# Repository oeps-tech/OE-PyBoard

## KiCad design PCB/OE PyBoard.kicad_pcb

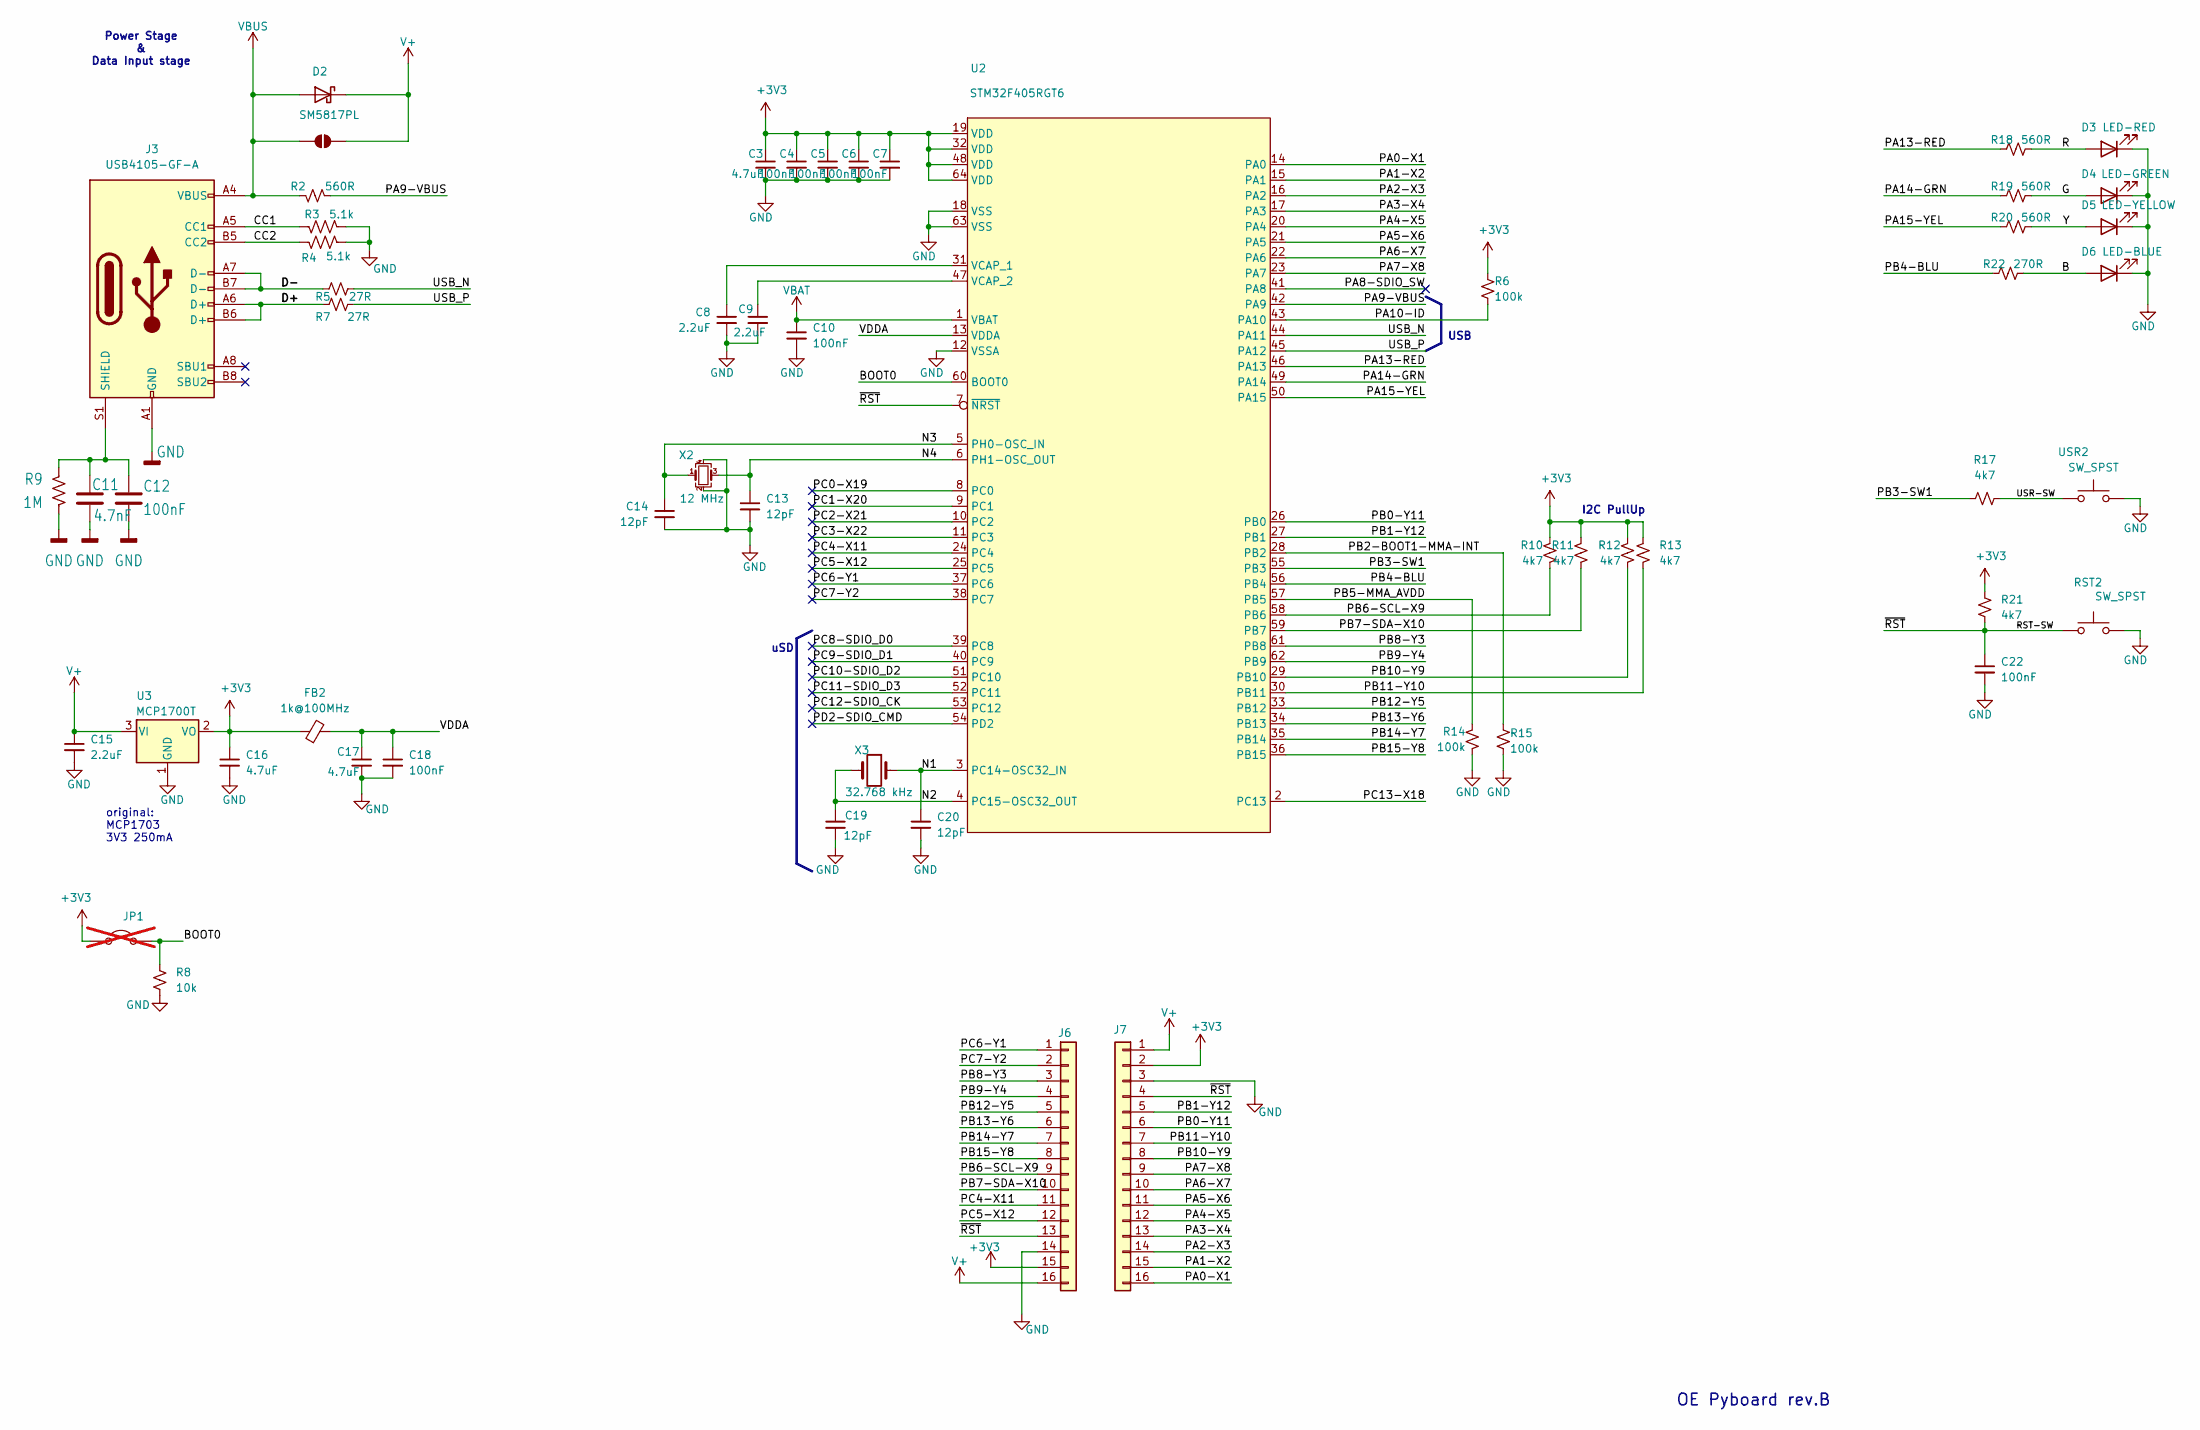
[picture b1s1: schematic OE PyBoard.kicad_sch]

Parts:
C3, C16, C17: 4.7uF; C_0603_1608Metric; MPN C1608X6S1C475K080AC
C4, C5, C6, C7, C10, C12, C18, C22: 100nF; C_0402_1005Metric; MPN CGA2B3X7R1H104K050BB
C8, C9, C15: 2.2uF; C_0603_1608Metric; MPN GRM188R61E225KA12D
C11: 4.7nF; C_0402_1005Metric; MPN 885012205084
C13, C14, C19, C20: 12pF; C_0402_1005Metric; MPN GRM1555C1H120JA01D
D2: SM5817PL; D_SOD-123; MPN SM5817PL-TP
D3: LED-RED; LED_0603_1608Metric; MPN 5990010007F
D4: LED-GREEN; LED_0603_1608Metric; MPN LSM0603453V
D5: LED-YELLOW; LED_0603_1608Metric; MPN 5990040007F
D6: LED-BLUE; LED_0603_1608Metric; MPN 5988D90107F
FB2: 1k@100MHz; L_0402_1005Metric; MPN BLM15HD102SN1D
J3: USB4105-GF-A; USB_C_Receptacle_GCT_USB4105-xx-A_16P_TopMnt_Horizontal; MPN USB4105-GF-A
J6, J7: Conn_01x08; PinHeader_1x16_P2.54mm_Vertical; MPN CES-116-01-T-S
JP1: Jumper; PinHeader_1x02_P2.54mm_Vertical; not fitted
JP2: 0R; SolderJumper-2_P1.3mm_Open_RoundedPad1.0x1.5mm
R2, R18, R19, R20: 560R; R_0402_1005Metric; MPN CRCW0402560RFKED
R3, R4: 5.1k; R_0402_1005Metric; MPN ERJ-2RKF5101X
R5, R7: 27R; R_0402_1005Metric; MPN RMCF0402FT27R0
R6, R14, R15: 100k; R_0402_1005Metric; MPN AC0402FR-07100KL
R8: 10k; R_0402_1005Metric; MPN ERJ-2RKF1002X
R9: 1M; R_0402_1005Metric; MPN CRCW04021M00FKED
R10, R11, R12, R13, R17, R21: 4k7; R_0402_1005Metric; MPN ERJ-2RKF4701X
R22: 270R; R_0402_1005Metric; MPN CRCW0402270RFKEDC
RST2: SW_SPST; SW_SPST_TL3305B; MPN TL3305BF260QG
U2: STM32F405RGT6; LQFP-64_10x10mm_P0.5mm; MPN STM32F405RGT6
U3: MCP1700T; SOT-23; MPN MCP1700T-3302E/TT
USR2: SW_SPST; SW_SPST_TL3305B; MPN TL3305BF260QG
X2: 12 MHz; Crystal_SMD_Abracon_ABM8AIG-4Pin_3.2x2.5mm; MPN ABM8AIG-12.000MHZ-12-2Z-T3
X3: 32.768 kHz; Crystal_SMD_2012-2Pin_2.0x1.2mm_HandSoldering; MPN 9HT11-32.768KBZF-T

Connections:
+3V3: C3.1, C4.1, C5.1, C6.1, C7.1, C16.1, FB2.1, J6.15, J7.2, JP1.2 (B), R6.1, R10.1, R11.1, R12.1, R13.1, R21.2, U2.19 (VDD), U2.32 (VDD), U2.48 (VDD), U2.64 (VDD), U3.2 (VO)
/B: D6.2 (A), R22.2
/BOOT0: JP1.1 (A), R8.1, U2.60 (BOOT0)
/CC1: J3.A5 (CC1), R3.1
/CC2: J3.B5 (CC2), R4.1
/D+: J3.A6 (D+), J3.B6 (D+), R7.2
/D-: J3.A7 (D-), J3.B7 (D-), R5.2
/G: D4.2 (A), R19.2
/N3: C14.1, U2.5 (PH0-OSC_IN), X2.1
/N4: C13.1, U2.6 (PH1-OSC_OUT), X2.3
/PA0-X1: J7.16, U2.14 (PA0)
/PA1-X2: J7.15, U2.15 (PA1)
/PA2-X3: J7.14, U2.16 (PA2)
/PA3-X4: J7.13, U2.17 (PA3)
/PA4-X5: J7.12, U2.20 (PA4)
/PA5-X6: J7.11, U2.21 (PA5)
/PA6-X7: J7.10, U2.22 (PA6)
/PA7-X8: J7.9, U2.23 (PA7)
/PA8-SDIO_SW: U2.41 (PA8)
/PA9-VBUS: R2.1, U2.42 (PA9)
/PA10-ID: R6.2, U2.43 (PA10)
/PA13-RED: R18.1, U2.46 (PA13)
/PA14-GRN: R19.1, U2.49 (PA14)
/PA15-YEL: R20.1, U2.50 (PA15)
/PB0-Y11: J7.6, U2.26 (PB0)
/PB1-Y12: J7.5, U2.27 (PB1)
/PB2-BOOT1-MMA-INT: R15.1, U2.28 (PB2)
/PB3-SW1: R17.1, U2.55 (PB3)
/PB4-BLU: R22.1, U2.56 (PB4)
/PB5-MMA_AVDD: R14.1, U2.57 (PB5)
/PB6-SCL-X9: J6.9, R10.2, U2.58 (PB6)
/PB7-SDA-X10: J6.10, R11.2, U2.59 (PB7)
/PB8-Y3: J6.3, U2.61 (PB8)
/PB9-Y4: J6.4, U2.62 (PB9)
/PB10-Y9: J7.8, R12.2, U2.29 (PB10)
/PB11-Y10: J7.7, R13.2, U2.30 (PB11)
/PB12-Y5: J6.5, U2.33 (PB12)
/PB13-Y6: J6.6, U2.34 (PB13)
/PB14-Y7: J6.7, U2.35 (PB14)
/PB15-Y8: J6.8, U2.36 (PB15)
/PC0-X19: U2.8 (PC0)
/PC1-X20: U2.9 (PC1)
/PC2-X21: U2.10 (PC2)
/PC3-X22: U2.11 (PC3)
/PC4-X11: J6.11, U2.24 (PC4)
/PC5-X12: J6.12, U2.25 (PC5)
/PC6-Y1: J6.1, U2.37 (PC6)
/PC7-Y2: J6.2, U2.38 (PC7)
/PC8-SDIO_D0: U2.39 (PC8)
/PC9-SDIO_D1: U2.40 (PC9)
/PC10-SDIO_D2: U2.51 (PC10)
/PC11-SDIO_D3: U2.52 (PC11)
/PC12-SDIO_CK: U2.53 (PC12)
/PC13-X18: U2.2 (PC13)
/PD2-SDIO_CMD: U2.54 (PD2)
/R: D3.2 (A), R18.2
/RST-SW: C22.1, J6.13, J7.4, R21.1, RST2.1, U2.7 (~NRST)
/USB_N: R5.1, U2.44 (PA11)
/USB_P: R7.1, U2.45 (PA12)
/USR-SW: R17.2, USR2.1
/VDDA: C17.1, C18.1, FB2.2, U2.13 (VDDA)
/Y: D5.2 (A), R20.2
GND: C3.2, C4.2, C5.2, C6.2, C7.2, C8.2, C9.2, C10.2, C11.2, C12.1, C13.2, C14.2, C15.2, C16.2, C17.2, C18.2, C19.2, C20.2, C22.2, D3.1 (K), D4.1 (K), D5.1 (K), D6.1 (K), J3.A1 (GND), J3.A12 (GND), J3.B1 (GND), J3.B12 (GND), J6.14, J7.3, R3.2, R4.2, R8.2, R9.1, R14.2, R15.2, RST2.2, U2.12 (VSSA), U2.18 (VSS), U2.63 (VSS), U3.1 (GND), USR2.2, X2.2, X2.4
unnamed: C11.1, C12.2, J3.S1 (SHIELD), R9.2
unnamed: C8.1, U2.31 (VCAP_1)
unnamed: C9.1, U2.47 (VCAP_2)
V+: C15.1, D2.1 (K), J6.16, J7.1, JP2.2 (B), U3.3 (VI)
VBAT: C10.1, U2.1 (VBAT)
VBUS: D2.2 (A), J3.A4 (VBUS), J3.A9 (VBUS), J3.B4 (VBUS), J3.B9 (VBUS), JP2.1 (A), R2.2

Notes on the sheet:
I2C PullUp
USB
original: MCP1703 3V3 250mA
uSD
OE Pyboard rev.B
Power Stage & Data Input stage

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
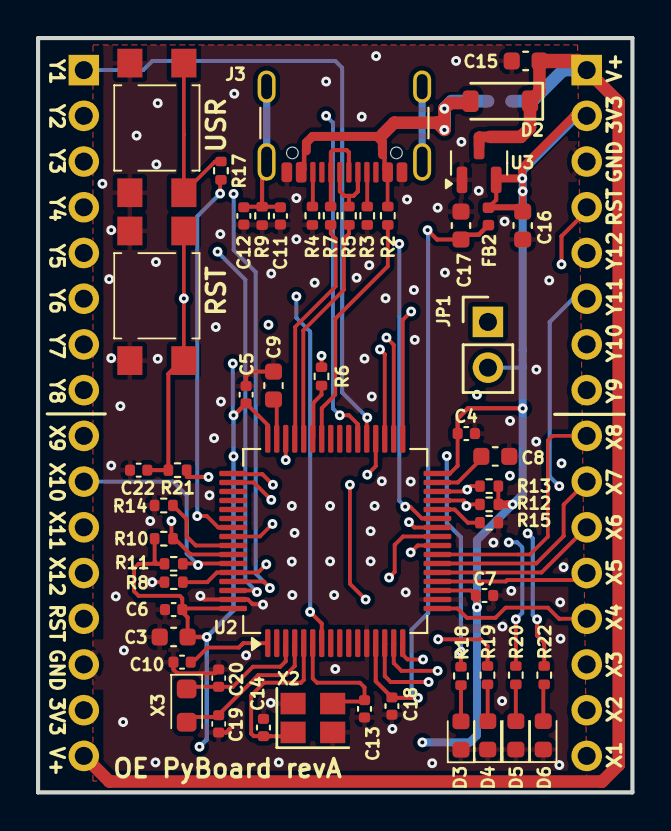
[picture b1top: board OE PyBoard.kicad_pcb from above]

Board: 4 copper layers, 33.0 x 41.9 mm, 56 parts (1 on the bottom side), 59 nets.

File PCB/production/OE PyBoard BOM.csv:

#;Reference;Qty;Value;Footprint;DNP;OEPSPN;MPN
1;C11;1;4.7nF;Capacitor_SMD:C_0402_1005Metric;;OEPS010017;885012205084
2;C13,C14,C19,C20;4;12pF;Capacitor_SMD:C_0402_1005Metric;;OEPS010086;GRM1555C1H120JA01D
3;C3,C16,C17;3;4.7uF;Capacitor_SMD:C_0603_1608Metric;;OEPS010018;C1608X6S1C475K080AC
4;C4,C5,C6,C7,C10,C12,C18,C22;8;100nF;Capacitor_SMD:C_0402_1005Metric;;OEPS010016;CGA2B3X7R1H104K050BB
5;C8,C9,C15;3;2.2uF;Capacitor_SMD:C_0603_1608Metric;;OEPS010075;GRM188R61E225KA12D
6;D2;1;SM5817PL;Diode_SMD:D_SOD-123;;OEPS030030;SM5817PL-TP
7;D3;1;LED-RED;LED_SMD:LED_0603_1608Metric;;OEPS030044;5990010007F
8;D4;1;LED-GREEN;LED_SMD:LED_0603_1608Metric;;OEPS030032;LSM0603453V
9;D5;1;LED-YELLOW;LED_SMD:LED_0603_1608Metric;;OEPS030043;5990040007F
10;D6;1;LED-BLUE;LED_SMD:LED_0603_1608Metric;;OEPS030042;5988D90107F
11;FB2;1;1k@100MHz;Inductor_SMD:L_0402_1005Metric;;OEPS040013;BLM15HD102SN1D
12;J3;1;USB4105-GF-A;Connector_USB:USB_C_Receptacle_GCT_USB4105-xx-A_16P_TopMnt_Horizontal;;OEPS070105;USB4105-GF-A
13;J6,J7;2;Conn_01x08;Connector_PinHeader_2.54mm:PinHeader_1x16_P2.54mm_Vertical;;OEPS070110;CES-116-01-T-S
14;JP1;1;Jumper;Connector_PinHeader_2.54mm:PinHeader_1x02_P2.54mm_Vertical;DNP;OEPS000000;
15;R8;1;10k;Resistor_SMD:R_0402_1005Metric;;OEPS020013;ERJ-2RKF1002X
16;R9;1;1M;Resistor_SMD:R_0402_1005Metric;;OEPS020026;CRCW04021M00FKED
17;R22;1;270R;Resistor_SMD:R_0402_1005Metric;;OEPS020060;CRCW0402270RFKEDC
18;R10,R11,R12,R13,R17,R21;6;4k7;Resistor_SMD:R_0402_1005Metric;;OEPS020010;ERJ-2RKF4701X
19;R2,R18,R19,R20;4;560R;Resistor_SMD:R_0402_1005Metric;;OEPS020193;CRCW0402560RFKED
20;R3,R4;2;5.1k;Resistor_SMD:R_0402_1005Metric;;OEPS020173;ERJ-2RKF5101X
21;R5,R7;2;27R;Resistor_SMD:R_0402_1005Metric;;OEPS020170;RMCF0402FT27R0
22;R6,R14,R15;3;100k;Resistor_SMD:R_0402_1005Metric;;OEPS020051;AC0402FR-07100KL
23;RST2,USR2;2;SW_SPST;Button_Switch_SMD:SW_SPST_TL3305B;;OEPS100061;TL3305BF260QG
24;U2;1;STM32F405RGT6;Package_QFP:LQFP-64_10x10mm_P0.5mm;;OEPS080178;STM32F405RGT6
25;U3;1;MCP1700T;Package_TO_SOT_SMD:SOT-23;;OEPS080153;MCP1700T-3302E/TT
26;X2;1;12 MHz;Crystal:Crystal_SMD_Abracon_ABM8AIG-4Pin_3.2x2.5mm;;OEPS100059;ABM8AIG-12.000MHZ-12-2Z-T3
27;X3;1;32.768 kHz;Crystal:Crystal_SMD_2012-2Pin_2.0x1.2mm_HandSoldering;;OEPS100051;9HT11-32.768KBZF-T

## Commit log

2025-08-28 Added .gitignore for KiCad project files
    Introduces a .gitignore file tailored for KiCad PCB design projects, excluding temporary, backup, netlist, autorouter, and exported BOM files to keep the repository clean.
2025-09-12 Updated .gitignore
2025-09-12 Added OE PyBoard initial KiCad project files
    Initial commit of OE PyBoard project including schematic, PCB, symbol and footprint libraries, 3D models, BOM, position files, drill files, and Gerber files for production.
2025-09-24 Added 3D model for SW_SPST_TL3305B and updated PCB
2025-09-25 Replaced D3 obsolete red LED in schematic, PCB, and BOM.
2025-10-02 Moved PyBoard files into PCB directory
    Renamed and reorganized all OE PyBoard-related files and production outputs into the PCB directory for improved project structure and clarity.
2025-10-02 Added firmware
2025-10-09 Fixed cristal and diode's footprint.
    Also, updated the production files.
2025-11-12 Isolated used analog lines and moved buttons
    Note: Gerbers and PnP files are not updated.
2025-11-24 Updated production files.
2025-11-24 Removed board stackup table from F.Fab layer
    Updated Gerber files to reflect these change.
